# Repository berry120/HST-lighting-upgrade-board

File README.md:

# HST-lighting-upgrade-board

A PCB allowing the lighting to be upgraded from the standard bulb - fits the old Hornby/Lima class 43 (Intercity 125) with the ringfield motor.

Distributed as an Eagle project.

For analogue operation, ignore PAD3 (DCC common) at the bottom, and solder wires from each rail to the two pads at the top.

For DCC operation, assuming standard wiring conventions, connect the blue wire to DCC common, the white wire to the left hand pad at the top, and the yellow wire to the right hand pad at the top.

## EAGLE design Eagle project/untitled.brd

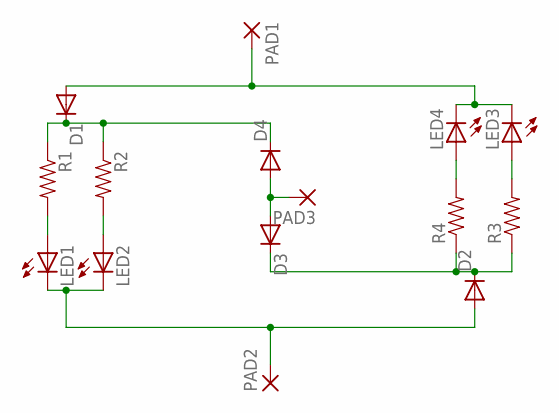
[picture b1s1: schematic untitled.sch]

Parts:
D1, D2, D3, D4: DIODE-DO-214AC; DO-214AC
LED1, LED2, LED3, LED4: LEDCHIP-LED0805; CHIP-LED0805
PAD1, PAD2, PAD3: 2,15/1,0
R1, R2, R3, R4: RESISTOR0805-RES; 0805

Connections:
unnamed: D2.C, D3.C, R3.1, R4.1
unnamed: D1.C, D4.C, R1.1, R2.1
unnamed: LED3.A, R3.2
unnamed: LED4.A, R4.2
unnamed: D2.A, LED1.C, LED2.C, PAD2.1
unnamed: D3.A, D4.A, PAD3.1
unnamed: LED2.A, R2.2
unnamed: LED1.A, R1.2
RED_CATHODE: D1.A, LED3.C, LED4.C, PAD1.1

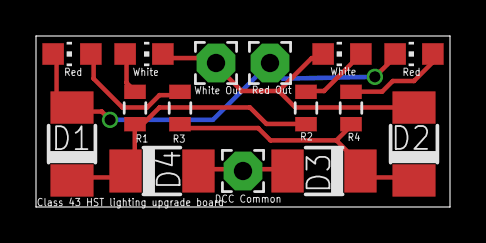
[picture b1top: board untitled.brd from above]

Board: 2 copper layers, 23.0 x 9.5 mm, 15 parts (0 on the bottom side), 9 nets.

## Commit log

2019-01-19 Move eagle project into separate folder
2019-01-19 Language classification fix
2019-01-31 Add schematic.png
2019-07-16 Add Codacy badge

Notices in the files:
parts and their libraries:
SparkFun: Licensing: CC v3.0 Share-Alike You are welcome to use this library for commercial purposes.
